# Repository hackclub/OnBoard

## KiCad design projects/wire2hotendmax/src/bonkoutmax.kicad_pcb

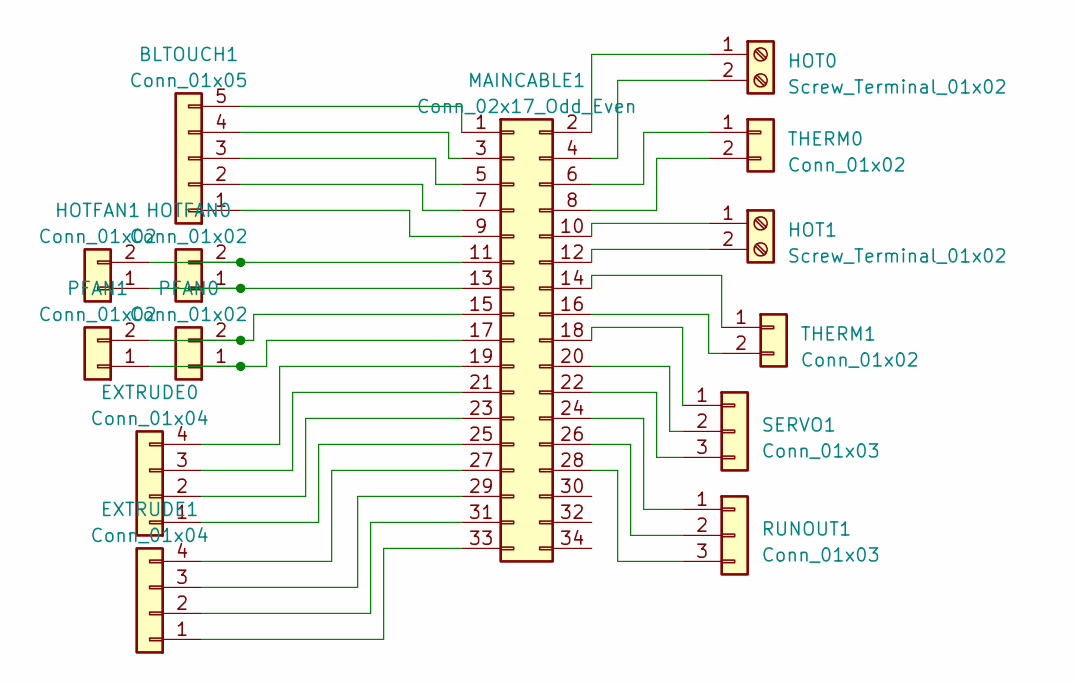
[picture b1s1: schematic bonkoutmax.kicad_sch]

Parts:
BLTOUCH1: Conn_01x05; JST_XH_B5B-XH-AM_1x05_P2.50mm_Vertical
EXTRUDE0, EXTRUDE1: Conn_01x04; JST_XH_B4B-XH-AM_1x04_P2.50mm_Vertical
HOT0, HOT1: Screw_Terminal_01x02; TerminalBlock_Phoenix_PT-1,5-2-3.5-H_1x02_P3.50mm_Horizontal
HOTFAN0, HOTFAN1: Conn_01x02; JST_XH_B2B-XH-AM_1x02_P2.50mm_Vertical
MAINCABLE1: Conn_02x17_Odd_Even; JST_PHD_S34B-PHDSS_2x17_P2.00mm_Horizontal
PFAN0, PFAN1: Conn_01x02; JST_XH_B2B-XH-AM_1x02_P2.50mm_Vertical
RUNOUT1: Conn_01x03; JST_XH_B3B-XH-AM_1x03_P2.50mm_Vertical
SERVO1: Conn_01x03; JST_XH_B3B-XH-AM_1x03_P2.50mm_Vertical
THERM0, THERM1: Conn_01x02; JST_XH_B2B-XH-AM_1x02_P2.50mm_Vertical

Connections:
unnamed: BLTOUCH1.1, MAINCABLE1.9
unnamed: BLTOUCH1.2, MAINCABLE1.7
unnamed: BLTOUCH1.3, MAINCABLE1.5
unnamed: BLTOUCH1.4, MAINCABLE1.3
unnamed: BLTOUCH1.5, MAINCABLE1.1
unnamed: EXTRUDE0.1, MAINCABLE1.25
unnamed: EXTRUDE0.2, MAINCABLE1.23
unnamed: EXTRUDE0.3, MAINCABLE1.21
unnamed: EXTRUDE0.4, MAINCABLE1.19
unnamed: EXTRUDE1.1, MAINCABLE1.33
unnamed: EXTRUDE1.2, MAINCABLE1.31
unnamed: EXTRUDE1.3, MAINCABLE1.29
unnamed: EXTRUDE1.4, MAINCABLE1.27
unnamed: HOT0.1, MAINCABLE1.2
unnamed: HOT0.2, MAINCABLE1.4
unnamed: HOT1.1, MAINCABLE1.10
unnamed: HOT1.2, MAINCABLE1.12
unnamed: HOTFAN0.1, HOTFAN1.1, MAINCABLE1.13
unnamed: HOTFAN0.2, HOTFAN1.2, MAINCABLE1.11
unnamed: MAINCABLE1.6, THERM0.1
unnamed: MAINCABLE1.8, THERM0.2
unnamed: MAINCABLE1.14, THERM1.1
unnamed: MAINCABLE1.15, PFAN0.2, PFAN1.2
unnamed: MAINCABLE1.16, THERM1.2
unnamed: MAINCABLE1.17, PFAN0.1, PFAN1.1
unnamed: MAINCABLE1.18, SERVO1.1
unnamed: MAINCABLE1.20, SERVO1.2
unnamed: MAINCABLE1.22, SERVO1.3
unnamed: MAINCABLE1.24, RUNOUT1.1
unnamed: MAINCABLE1.26, RUNOUT1.2
unnamed: MAINCABLE1.28, RUNOUT1.3

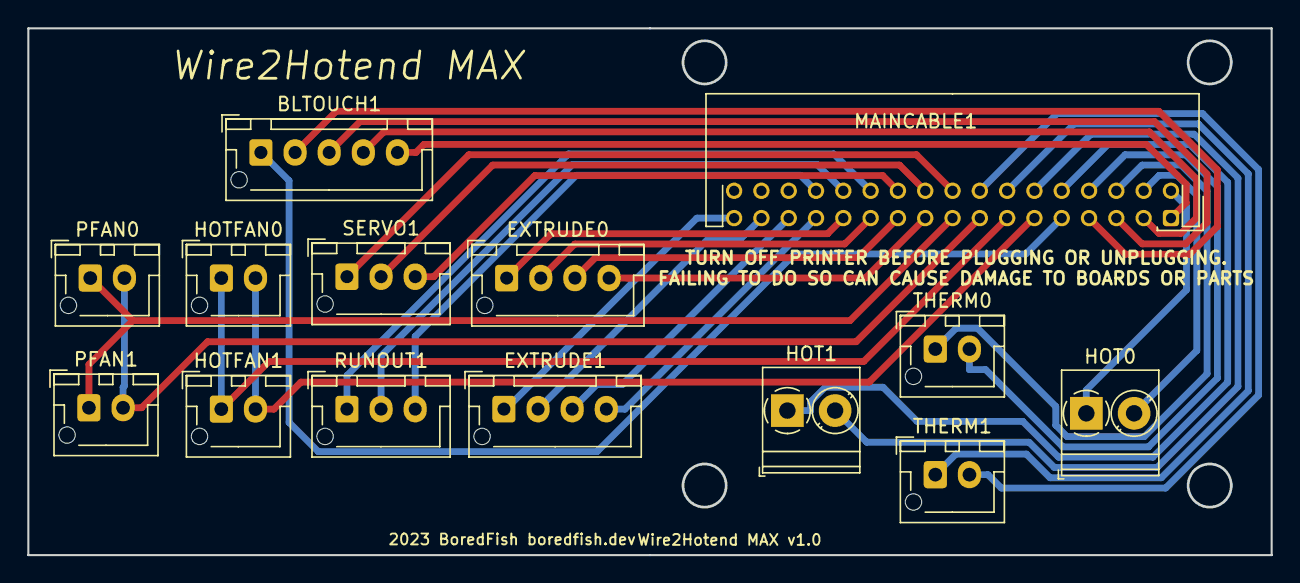
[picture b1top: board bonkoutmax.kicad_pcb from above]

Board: 2 copper layers, 91.1 x 38.6 mm, 14 parts (0 on the bottom side), 31 nets.

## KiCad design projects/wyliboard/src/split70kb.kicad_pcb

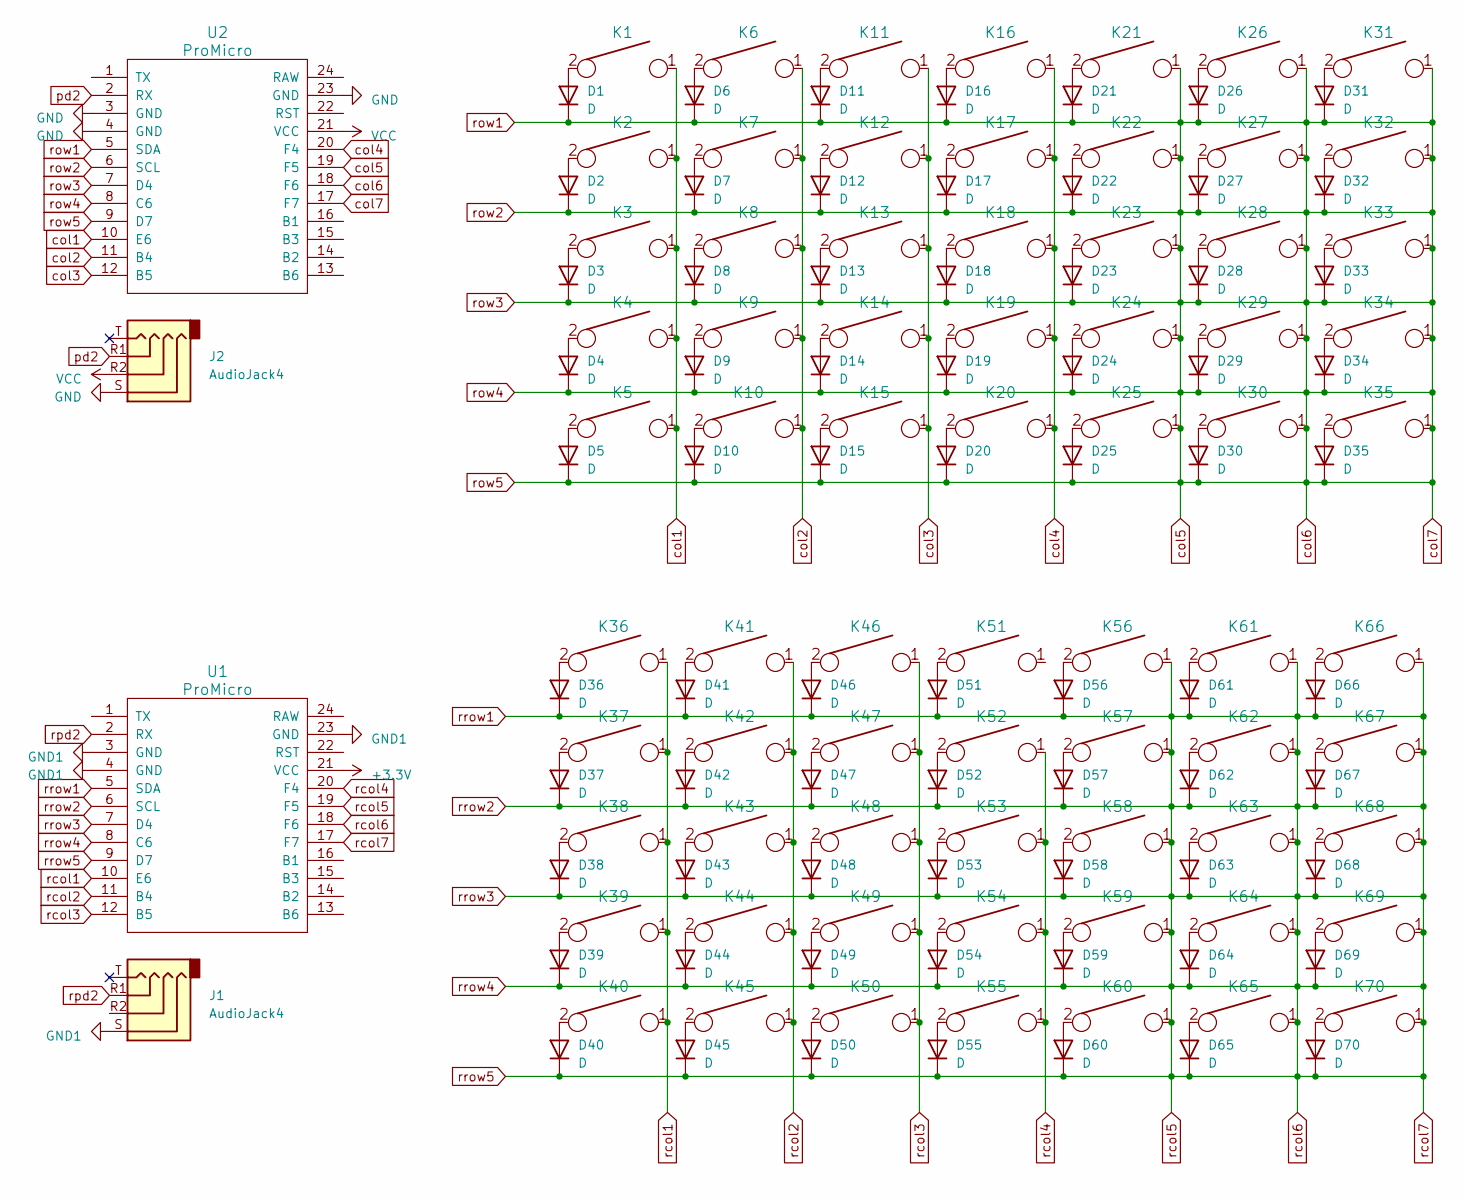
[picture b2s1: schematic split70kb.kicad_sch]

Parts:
D1: D; D_SOD123_axial; JLC 1N4148W
D2, D3, D4, D5, D6, D7, D8, D9, D10, D11, D12, D13, D14, D15, D16, D17, D18, D19, D20, D21, D22, D23, D24, D25, D26, D27, D28, D29, D30, D31, D32, D33, D34, D35, D36, D37, D38, D39, D40, D41, D42, D43, D44, D45, D46, D47, D48, D49, D50, D51, D52, D53, D54, D55, D56, D57, D58, D59, D60, D61, D62, D63, D64, D65, D66, D67, D68, D69, D70: D; D_SOD123_axial; LCSC C89641
J1, J2: AudioJack4; Jack_3.5mm_PJ320D_Horizontal
K1, K2, K3, K4, K5, K6, K7, K8, K9, K10, K11, K12, K13, K14, K15, K16, K17, K18, K19, K20, K21, K22, K23, K24, K25, K26, K27, K28, K29, K30, K31, K32, K33, K34, K35, K36, K37, K38, K39, K40, K41, K42, K43, K44, K45, K46, K47, K48, K49, K50, K51, K52, K53, K54, K55, K56, K57, K58, K59, K60, K61, K62, K63, K64, K65, K66, K67, K68, K69, K70: KEYSW; Mx_Alps_100
U1, U2: ProMicro; Pro_Micro

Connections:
+3.3V: U1.21 (VCC)
GND: J2.S, U2.3 (GND), U2.4 (GND), U2.23 (GND)
GND1: J1.S, U1.3 (GND), U1.4 (GND), U1.23 (GND)
unnamed: D1.2 (A), K1.2
unnamed: D2.2 (A), K2.2
unnamed: D3.2 (A), K3.2
unnamed: D4.2 (A), K4.2
unnamed: D5.2 (A), K5.2
unnamed: D6.2 (A), K6.2
unnamed: D7.2 (A), K7.2
unnamed: D8.2 (A), K8.2
unnamed: D9.2 (A), K9.2
unnamed: D10.2 (A), K10.2
unnamed: D11.2 (A), K11.2
unnamed: D12.2 (A), K12.2
unnamed: D13.2 (A), K13.2
unnamed: D14.2 (A), K14.2
unnamed: D15.2 (A), K15.2
unnamed: D16.2 (A), K16.2
unnamed: D17.2 (A), K17.2
unnamed: D18.2 (A), K18.2
unnamed: D19.2 (A), K19.2
unnamed: D20.2 (A), K20.2
unnamed: D21.2 (A), K21.2
unnamed: D22.2 (A), K22.2
unnamed: D23.2 (A), K23.2
unnamed: D24.2 (A), K24.2
unnamed: D25.2 (A), K25.2
unnamed: D26.2 (A), K26.2
unnamed: D27.2 (A), K27.2
unnamed: D28.2 (A), K28.2
unnamed: D29.2 (A), K29.2
unnamed: D30.2 (A), K30.2
unnamed: D31.2 (A), K31.2
unnamed: D32.2 (A), K32.2
unnamed: D33.2 (A), K33.2
unnamed: D34.2 (A), K34.2
unnamed: D35.2 (A), K35.2
unnamed: D36.2 (A), K36.2
unnamed: D37.2 (A), K37.2
unnamed: D38.2 (A), K38.2
unnamed: D39.2 (A), K39.2
unnamed: D40.2 (A), K40.2
unnamed: D41.2 (A), K41.2
unnamed: D42.2 (A), K42.2
unnamed: D43.2 (A), K43.2
unnamed: D44.2 (A), K44.2
unnamed: D45.2 (A), K45.2
unnamed: D46.2 (A), K46.2
unnamed: D47.2 (A), K47.2
unnamed: D48.2 (A), K48.2
unnamed: D49.2 (A), K49.2
unnamed: D50.2 (A), K50.2
unnamed: D51.2 (A), K51.2
unnamed: D52.2 (A), K52.2
unnamed: D53.2 (A), K53.2
unnamed: D54.2 (A), K54.2
unnamed: D55.2 (A), K55.2
unnamed: D56.2 (A), K56.2
unnamed: D57.2 (A), K57.2
unnamed: D58.2 (A), K58.2
unnamed: D59.2 (A), K59.2
unnamed: D60.2 (A), K60.2
unnamed: D61.2 (A), K61.2
unnamed: D62.2 (A), K62.2
unnamed: D63.2 (A), K63.2
unnamed: D64.2 (A), K64.2
unnamed: D65.2 (A), K65.2
unnamed: D66.2 (A), K66.2
unnamed: D67.2 (A), K67.2
unnamed: D68.2 (A), K68.2
unnamed: D69.2 (A), K69.2
unnamed: D70.2 (A), K70.2
VCC: J2.R2, U2.21 (VCC)
col1: K1.1, K2.1, K3.1, K4.1, K5.1, U2.10 (E6)
col2: K6.1, K7.1, K8.1, K9.1, K10.1, U2.11 (B4)
col3: K11.1, K12.1, K13.1, K14.1, K15.1, U2.12 (B5)
col4: K16.1, K17.1, K18.1, K19.1, K20.1, U2.20 (F4)
col5: D1.1 (K), D2.1 (K), D3.1 (K), D4.1 (K), D5.1 (K), D6.1 (K), D7.1 (K), D8.1 (K), D9.1 (K), D10.1 (K), D11.1 (K), D12.1 (K), D13.1 (K), D14.1 (K), D15.1 (K), D16.1 (K), D17.1 (K), D18.1 (K), D19.1 (K), D20.1 (K), D21.1 (K), D22.1 (K), D23.1 (K), D24.1 (K), D25.1 (K), D26.1 (K), D27.1 (K), D28.1 (K), D29.1 (K), D30.1 (K), D31.1 (K), D32.1 (K), D33.1 (K), D34.1 (K), D35.1 (K), K21.1, K22.1, K23.1, K24.1, K25.1, K26.1, K27.1, K28.1, K29.1, K30.1, K31.1, K32.1, K33.1, K34.1, K35.1, U2.5 (SDA), U2.6 (SCL), U2.7 (D4), U2.8 (C6), U2.9 (D7), U2.17 (F7), U2.18 (F6), U2.19 (F5)
pd2: J2.R1, U2.2 (RX)
rcol1: K36.1, K37.1, K38.1, K39.1, K40.1, U1.10 (E6)
rcol2: K41.1, K42.1, K43.1, K44.1, K45.1, U1.11 (B4)
rcol3: K46.1, K47.1, K48.1, K49.1, K50.1, U1.12 (B5)
rcol4: K51.1, K52.1, K53.1, K54.1, K55.1, U1.20 (F4)
rcol5: D36.1 (K), D37.1 (K), D38.1 (K), D39.1 (K), D40.1 (K), D41.1 (K), D42.1 (K), D43.1 (K), D44.1 (K), D45.1 (K), D46.1 (K), D47.1 (K), D48.1 (K), D49.1 (K), D50.1 (K), D51.1 (K), D52.1 (K), D53.1 (K), D54.1 (K), D55.1 (K), D56.1 (K), D57.1 (K), D58.1 (K), D59.1 (K), D60.1 (K), D61.1 (K), D62.1 (K), D63.1 (K), D64.1 (K), D65.1 (K), D66.1 (K), D67.1 (K), D68.1 (K), D69.1 (K), D70.1 (K), K56.1, K57.1, K58.1, K59.1, K60.1, K61.1, K62.1, K63.1, K64.1, K65.1, K66.1, K67.1, K68.1, K69.1, K70.1, U1.5 (SDA), U1.6 (SCL), U1.7 (D4), U1.8 (C6), U1.9 (D7), U1.17 (F7), U1.18 (F6), U1.19 (F5)
rpd2: J1.R1, U1.2 (RX)

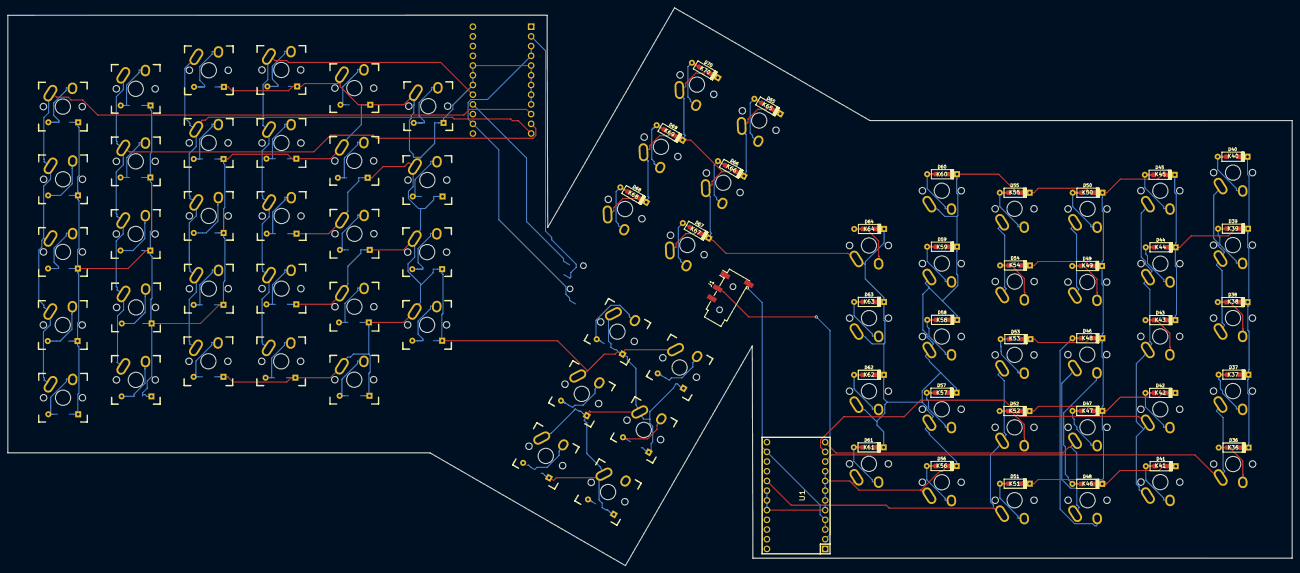
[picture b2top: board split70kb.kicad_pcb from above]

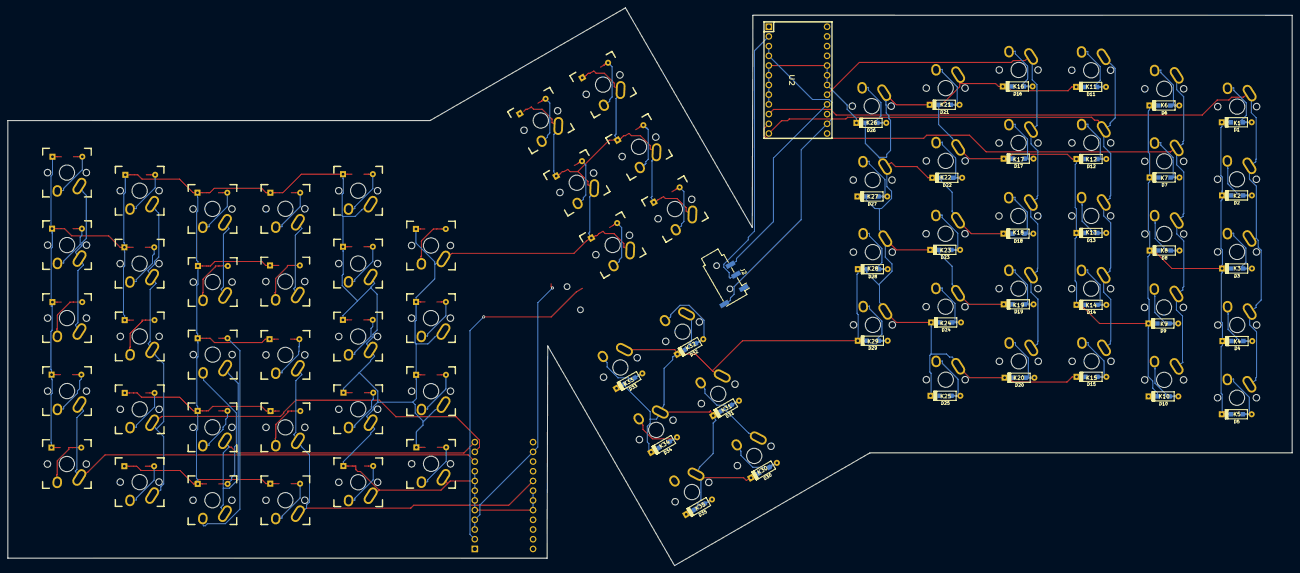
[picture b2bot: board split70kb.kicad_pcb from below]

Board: 2 copper layers, 335.9 x 145.9 mm, 144 parts (72 on the bottom side), 85 nets.

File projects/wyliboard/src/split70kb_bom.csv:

"Comment","Designator","Footprint","LCSC Part #"
"D","D1 D2 D3 D4 D5 D6 D7 D8 D9 D10 D11 D12 D13 D14 D15 D16 D17 D18 D19 D20 D21 D22 D23 D24 D25 D26 D27 D28 D29 D30 D31 D32 D33 D34 D35 D36 D37 D38 D39 D40 D41 D42 D43 D44 D45 D46 D47 D48 D49 D50 D51 D52 D53 D54 D55 D56 D57 D58 D59 D60 D61 D62 D63 D64 D65 D66 D67 D68 D69 D70","1N4148W","C89641"
"AudioJack4","J1 J2","",""
"KEYSW","K1 K2 K3 K4 K5 K6 K7 K8 K9 K10 K11 K12 K13 K14 K15 K16 K17 K18 K19 K20 K21 K22 K23 K24 K25 K26 K27 K28 K29 K30 K31 K32 K33 K34 K35 K36 K37 K38 K39 K40 K41 K42 K43 K44 K45 K46 K47 K48 K49 K50 K51 K52 K53 K54 K55 K56 K57 K58 K59 K60 K61 K62 K63 K64 K65 K66 K67 K68 K69 K70","",""
"ProMicro","U1 U2","",""

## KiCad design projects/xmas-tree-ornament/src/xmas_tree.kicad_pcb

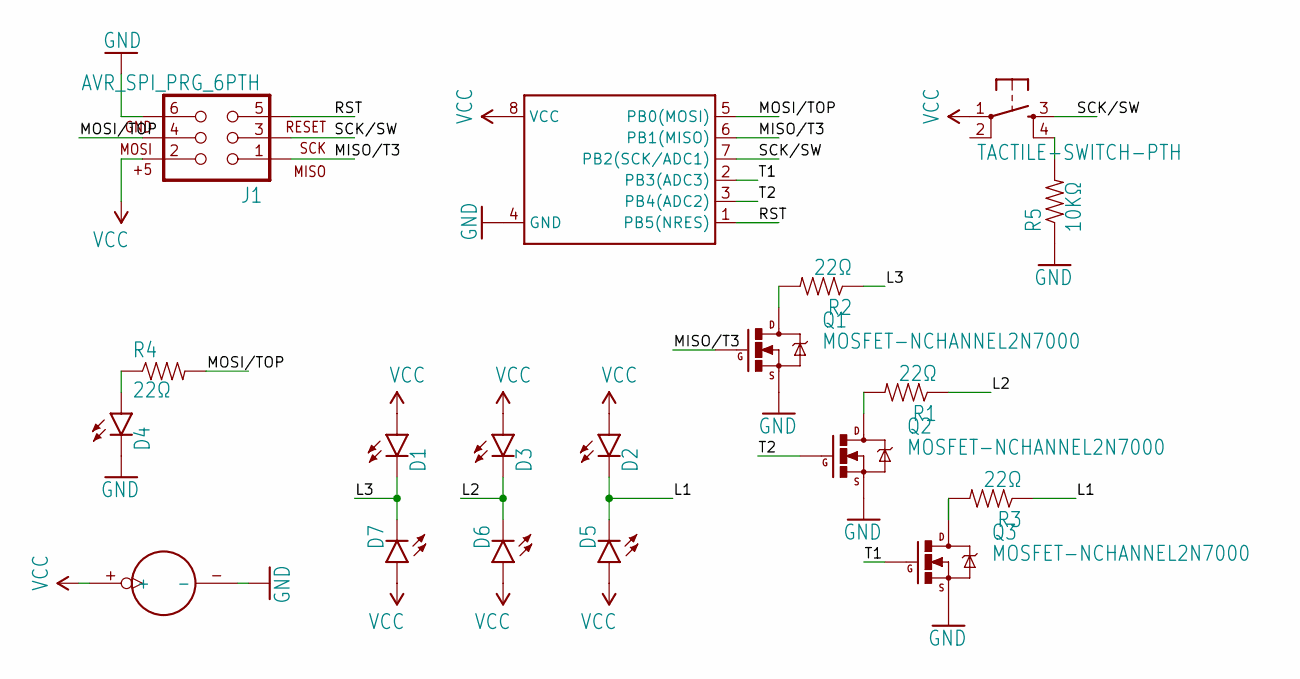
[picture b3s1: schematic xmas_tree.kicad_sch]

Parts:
BATTERY_1: BATTERY_1236_C
D1, D2, D3, D4, D5, D6, D7: LED; LED5MM-SLIM
J1: AVR_SPI_PRG_6PTH; 2X3
Q1, Q2, Q3: MOSFET-NCHANNEL2N7000; TO-92
R1, R2, R3, R4: 22Ω; 1206
R5: 10KΩ; 1206
U1: TINY45-20-DIP; DIP08
U$1: TACTILE-SWITCH-PTH; TAC-SWITCH-PTH

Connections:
GND: BATTERY_1.-, D4.K (C), J1.6, Q1.1 (S), Q2.1 (S), Q3.1 (S), R5.1, U1.4 (GND)
L1: D2.K (C), D5.K (C), R3.1
L2: D3.K (C), D6.K (C), R1.1
L3: D1.K (C), D7.K (C), R2.1
MISO/T3: J1.1, Q1.2 (G), U1.6 (PB1(MISO))
MOSI/TOP: J1.4, R4.2, U1.5 (PB0(MOSI))
unnamed: Q1.3 (D), R2.2
unnamed: R5.2, U$1.4
unnamed: Q2.3 (D), R1.2
unnamed: Q3.3 (D), R3.2
unnamed: D4.A, R4.1
RST: J1.5, U1.1 (PB5(NRES))
SCK/SW: J1.3, U1.7 (PB2(SCK/ADC1)), U$1.3
T1: Q3.2 (G), U1.2 (PB3(ADC3))
T2: Q2.2 (G), U1.3 (PB4(ADC2))
VCC: BATTERY_1.+, D1.A, D2.A, D3.A, D5.A, D6.A, D7.A, J1.2, U1.8 (VCC), U$1.1

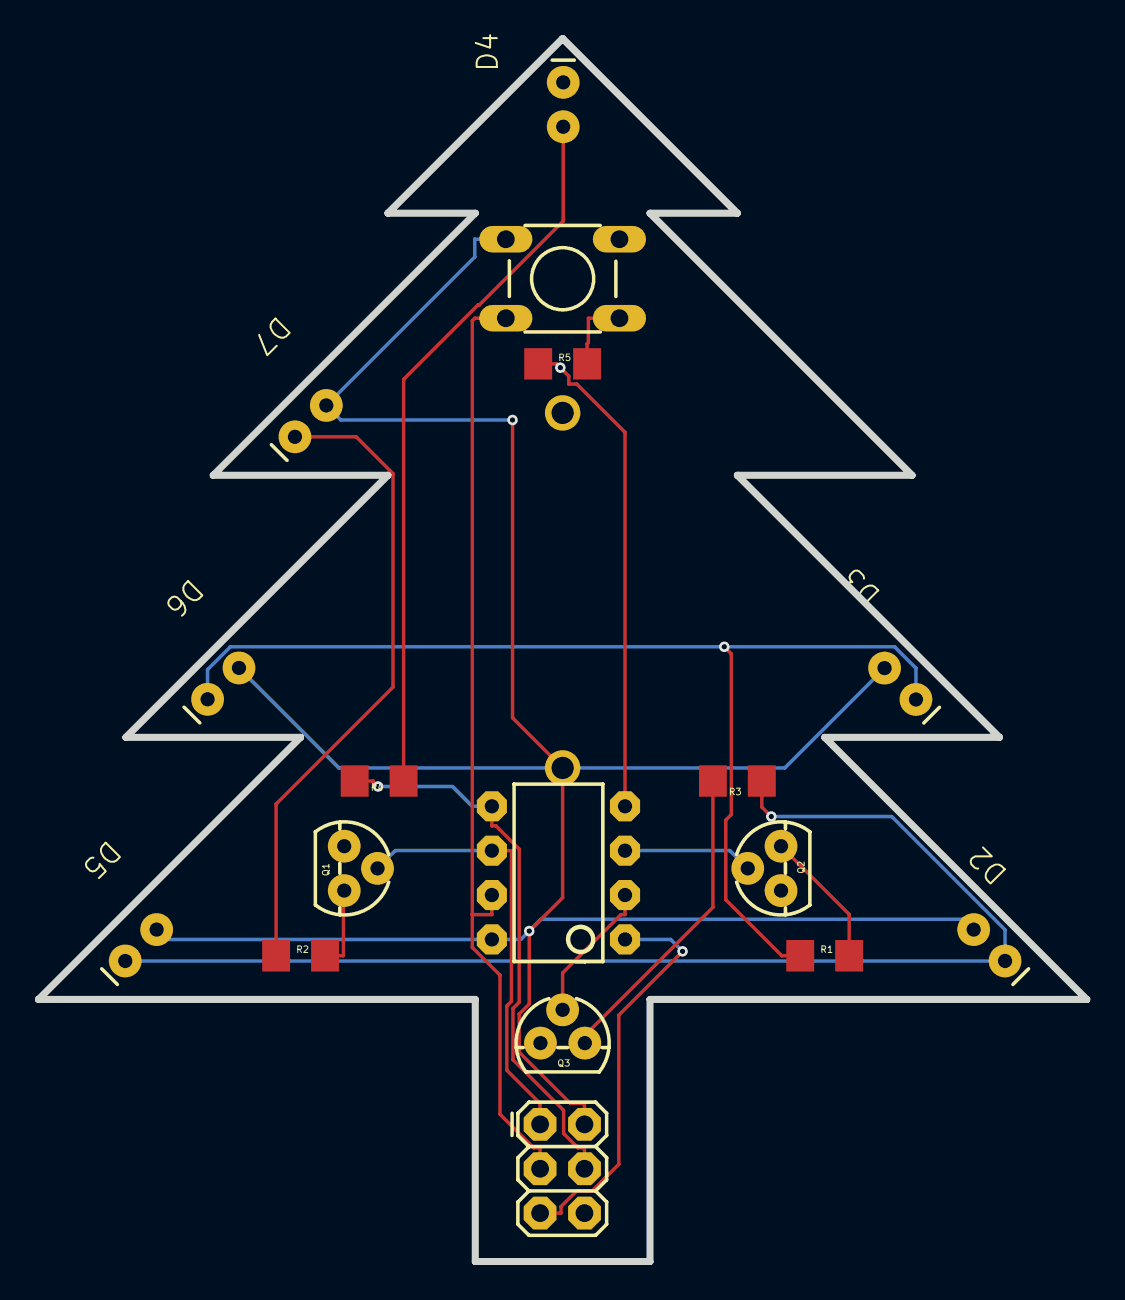
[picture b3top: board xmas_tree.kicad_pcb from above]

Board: 2 copper layers, 60.0 x 70.0 mm, 18 parts (1 on the bottom side), 16 nets.

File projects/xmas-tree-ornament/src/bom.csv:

"Id";"Designator";"Footprint";"Quantity";"Designation";"Supplier and ref";
1;"D4,D2,D5,D6,D3,D7";"LED5MM-SLIM";6;"";;;
2;"U1";"DIP08";1;"TINY45-20-DIP";;;
3;"Q2,Q1,Q3";"TO-92";3;"MOSFET-NCHANNEL2N7000";;;
4;"R5";"1206";1;"10KΩ";;;
5;"J1";"2X3";1;"AVR_SPI_PRG_6PTH";;;
6;"U$1";"TAC-SWITCH-PTH";1;"TACTILE-SWITCH-PTH";;;
7;"R4,R3,R1,R2";"1206";4;"22Ω";;;
8;"BATTERY_1";"BATTERY_1236_C";1;"BATTERY_1236_C";;;

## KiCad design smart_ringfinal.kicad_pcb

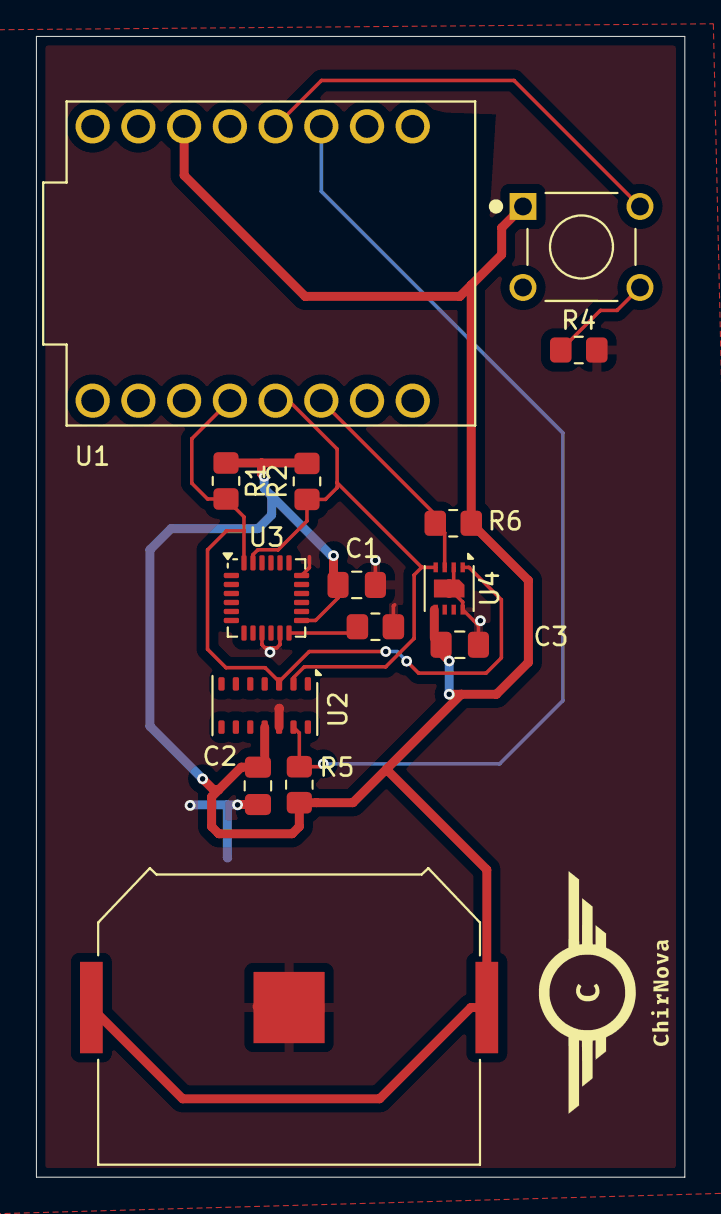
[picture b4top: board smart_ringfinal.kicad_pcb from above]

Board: 2 copper layers, 36.0 x 63.4 mm, 15 parts (0 on the bottom side), 9 nets.

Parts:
BT1: 3034; BAT_3034
C1, C2, C3: 0.1u; C_0805_2012Metric_Pad1.18x1.45mm_HandSolder
R1, R2, R5, R6: 4.7k; R_0805_2012Metric_Pad1.20x1.40mm_HandSolder
R3, R4: 10k; R_0805_2012Metric_Pad1.20x1.40mm_HandSolder
S1: FSM8JH; SW_FSM8JH
U1: ESP32-C3_SUPERMINI_TH; ESP32 C3_MINI
U2: MAX30102; Maxim_OLGA-14_3.3x5.6mm_P0.8mm
U3: MPU-6050; InvenSense_QFN-24_4x4mm_P0.5mm
U4: SHT30-DIS; Sensirion_DFN-8-1EP_2.5x2.5mm_P0.5mm_EP1.1x1.7mm

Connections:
3.3V: BT1.P1, BT1.P2, C1.2, C2.1, C3.2, R1.1, R2.2, R5.2, R6.2, S1.1, U1.3.3 (3V3), U2.11 (VDD), U3.13 (VDD), U4.5 (VDD)
GND: BT1.N, C1.1, C2.2, C3.1, R3.2, R4.2, U2.12 (GND), U3.9 (AD0), U3.11 (FSYNC), U3.18 (GND), U4.2 (ADDR), U4.8 (VSS), U4.9 (VSS)
unnamed: R4.1, S1.4
unnamed: R5.1, U1.2 (GPIO2), U2.13 (~INT)
unnamed: S1.3, U1.3 (GPIO3)
unnamed: R6.1, U1.10 (GPIO10), U4.3 (ALERT)
unnamed: R3.1, U3.12 (INT)
SCL: R2.1, U1.9 (GPIO9), U2.2 (SCL), U3.23 (SCL), U4.4 (SCL)
SDA: R1.2, U1.8 (GPIO8), U2.3 (SDA), U3.24 (SDA), U4.1 (SDA)
